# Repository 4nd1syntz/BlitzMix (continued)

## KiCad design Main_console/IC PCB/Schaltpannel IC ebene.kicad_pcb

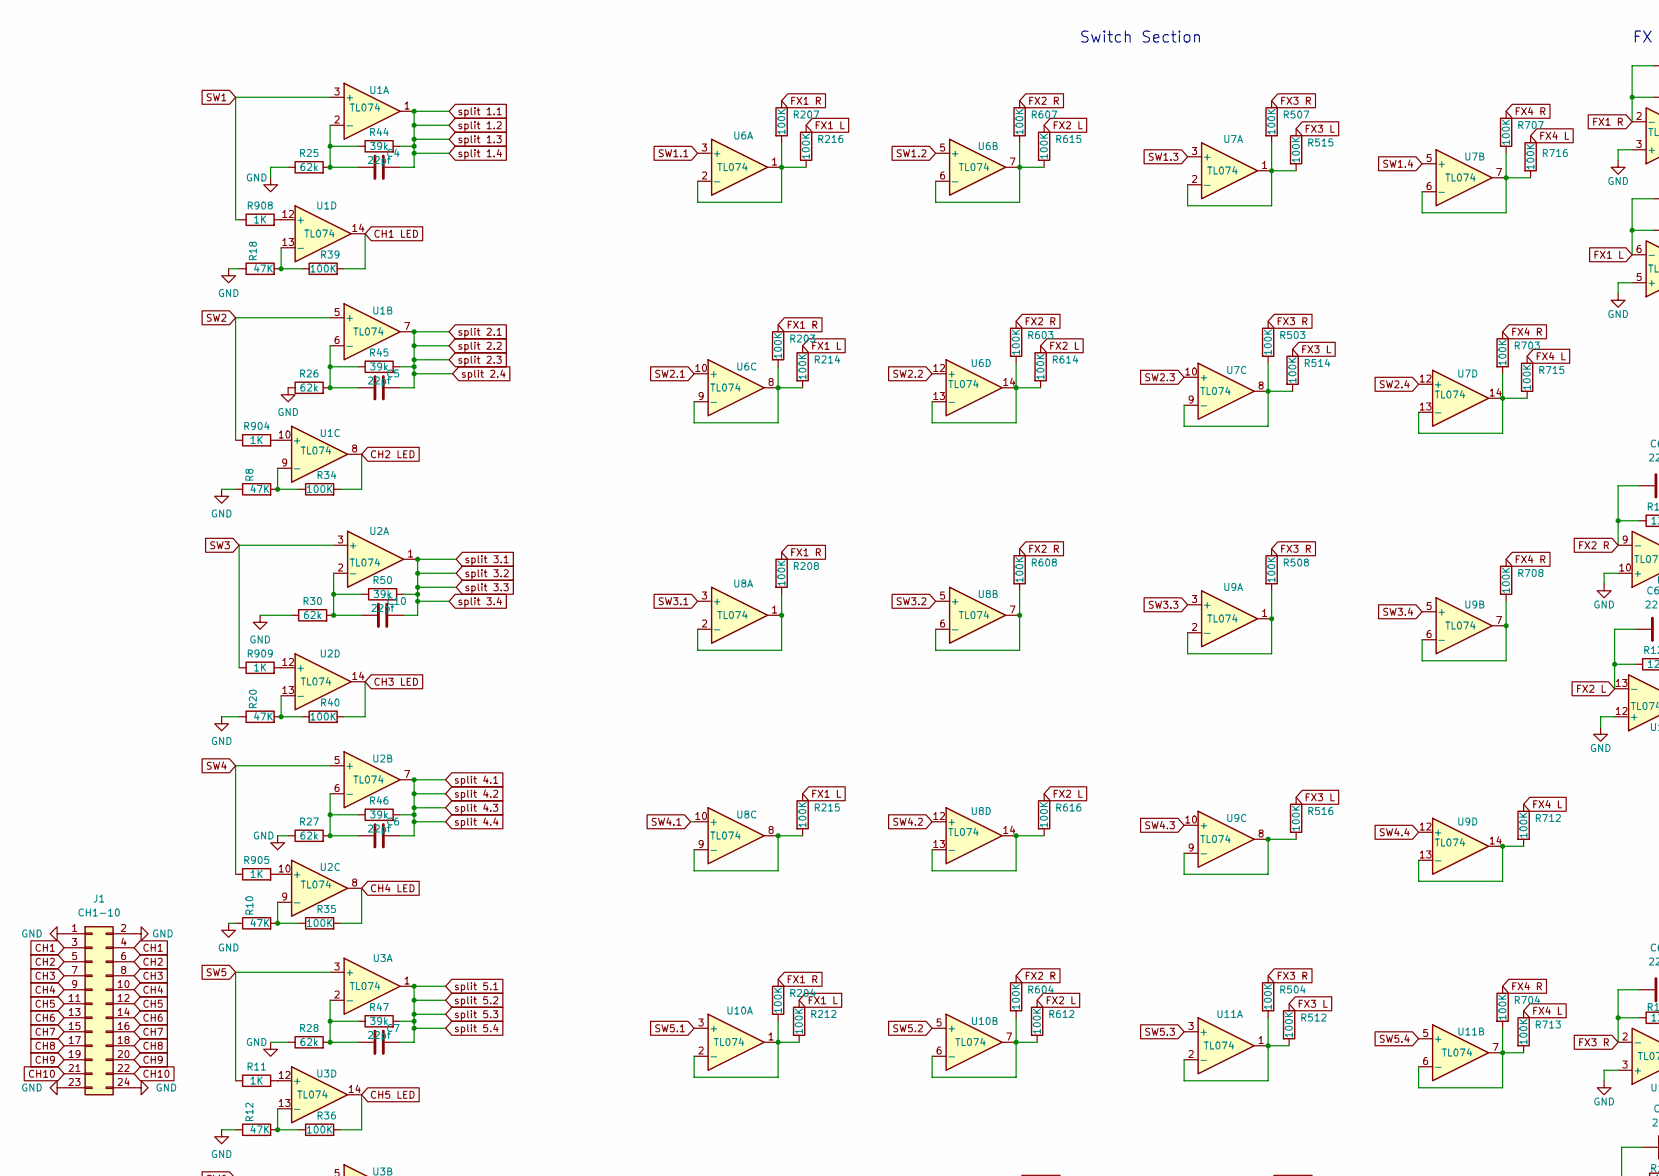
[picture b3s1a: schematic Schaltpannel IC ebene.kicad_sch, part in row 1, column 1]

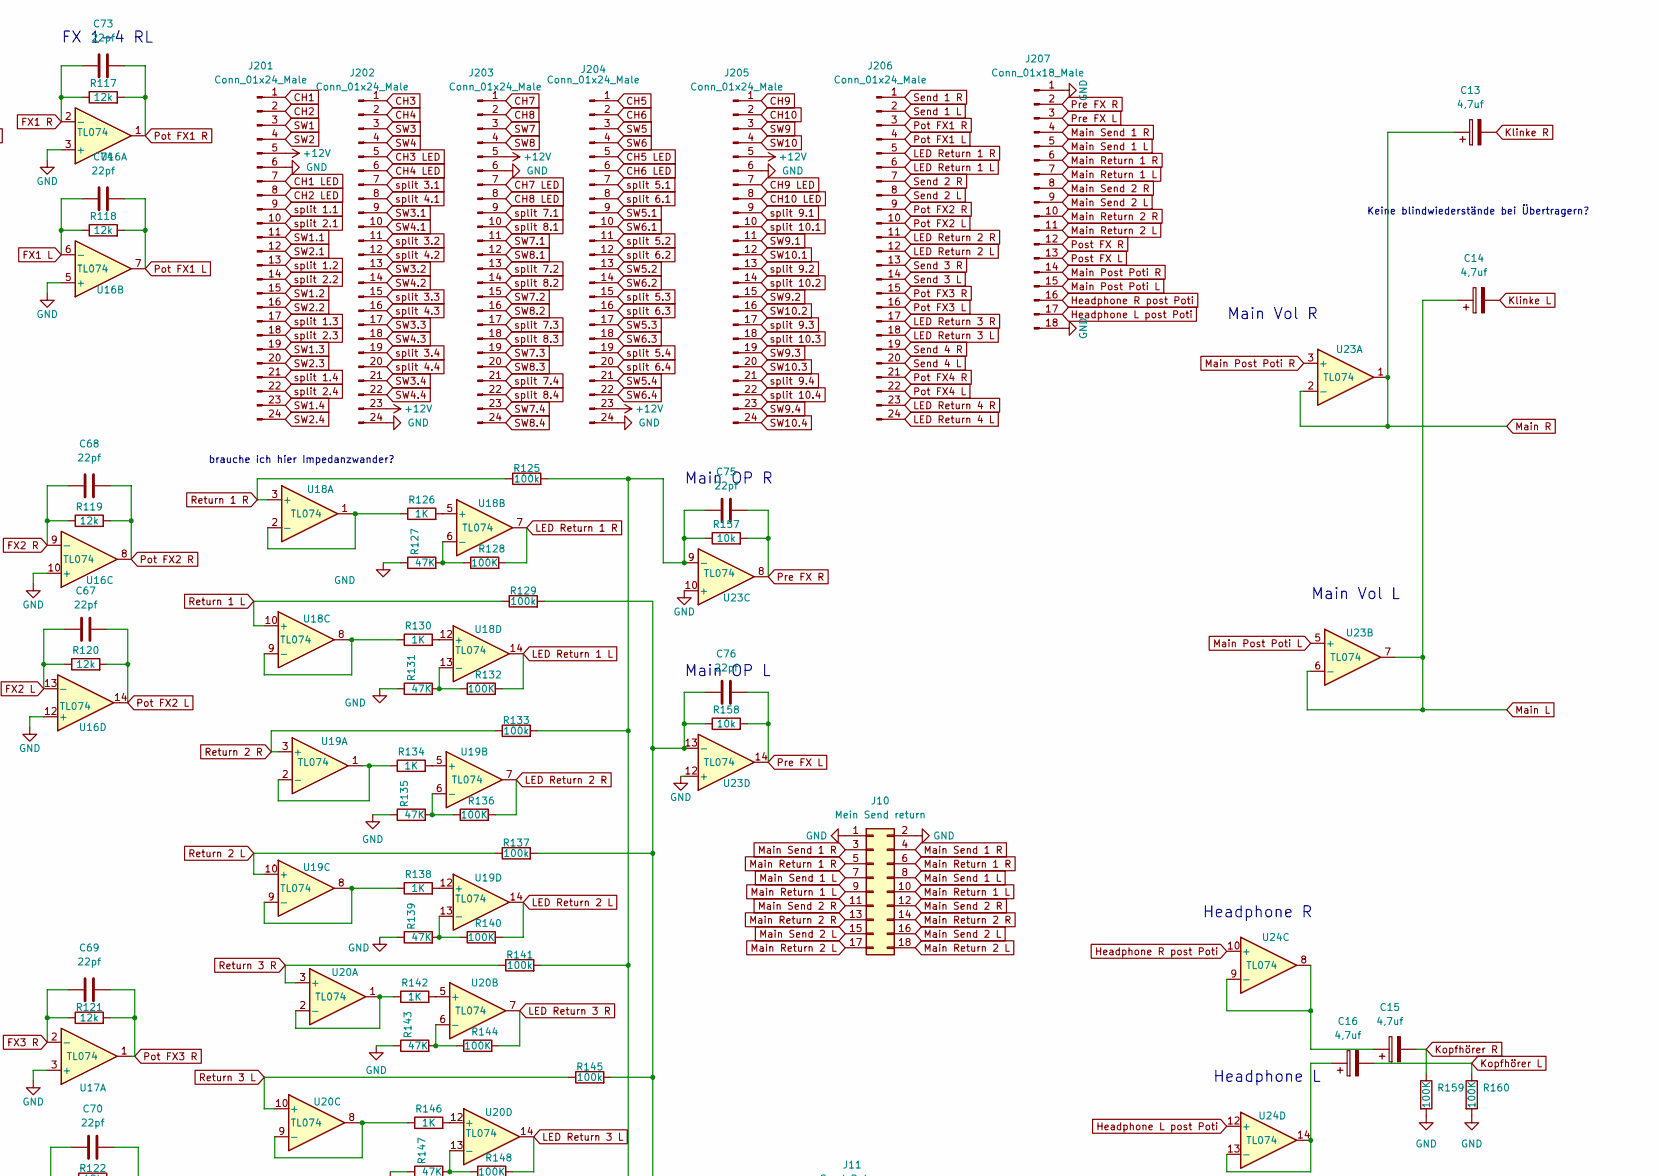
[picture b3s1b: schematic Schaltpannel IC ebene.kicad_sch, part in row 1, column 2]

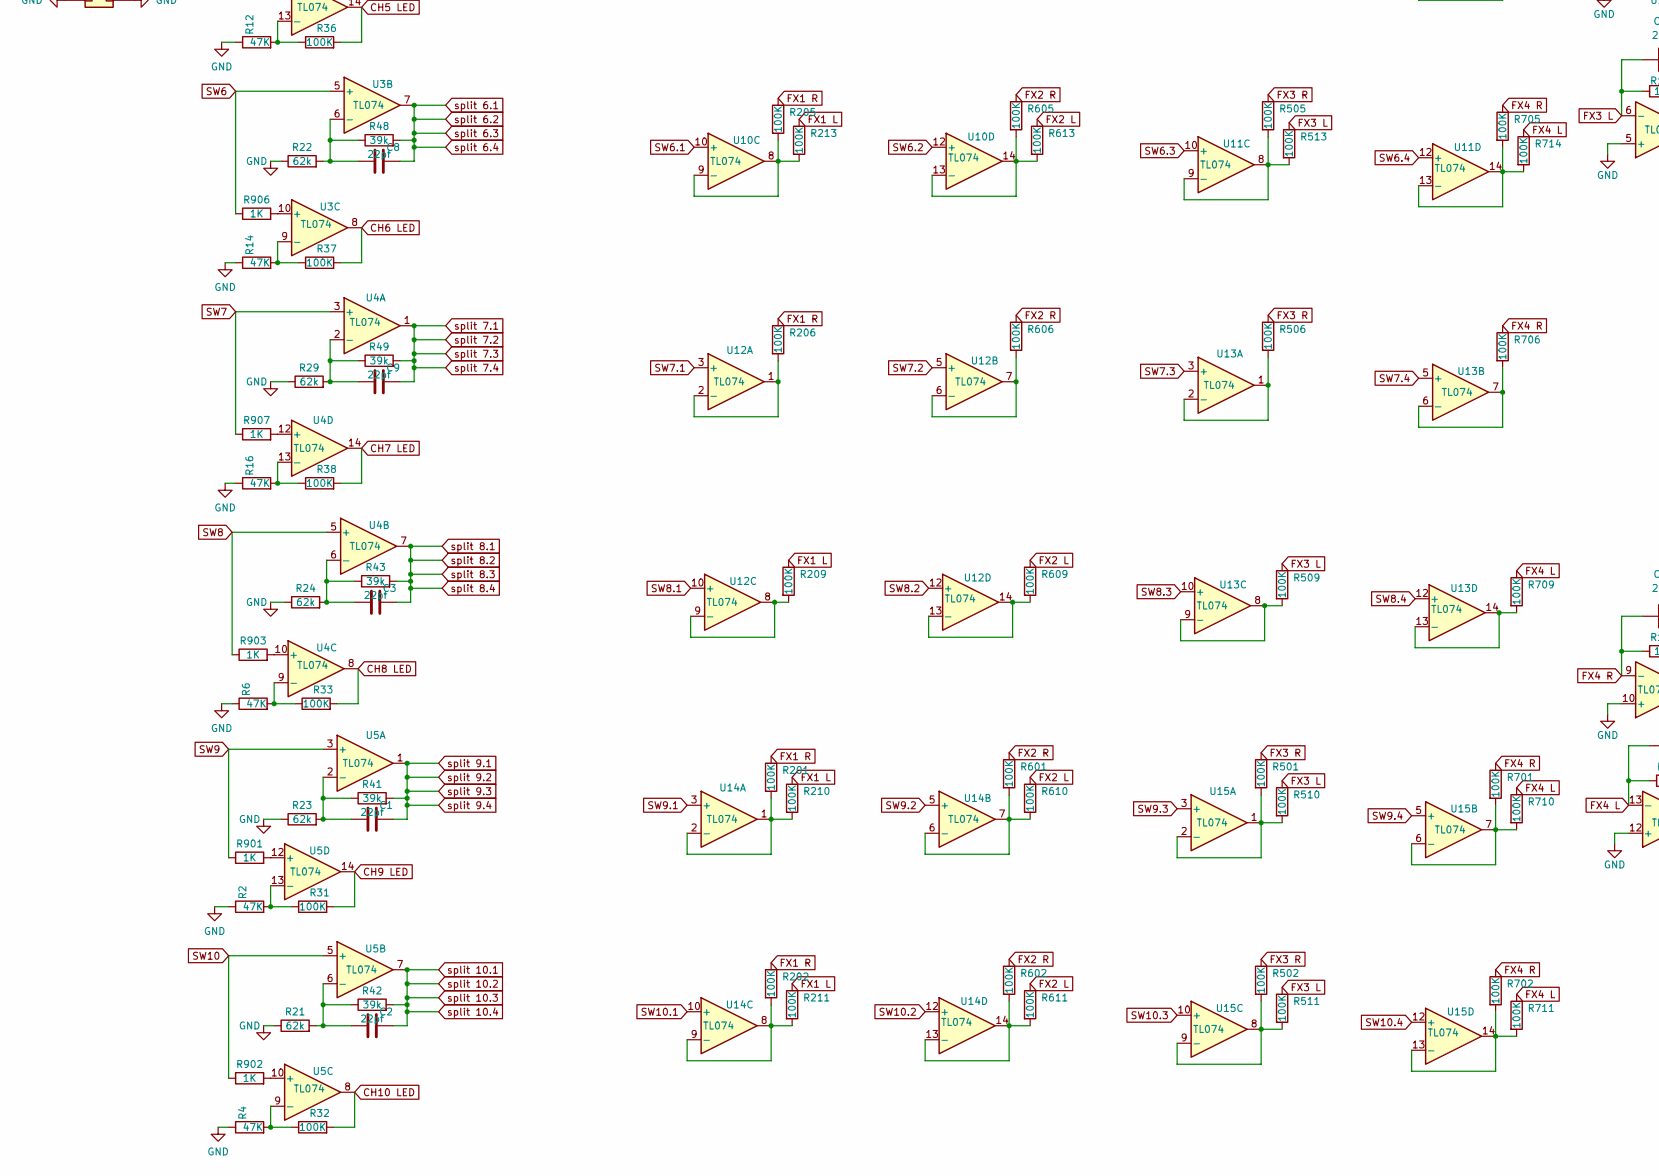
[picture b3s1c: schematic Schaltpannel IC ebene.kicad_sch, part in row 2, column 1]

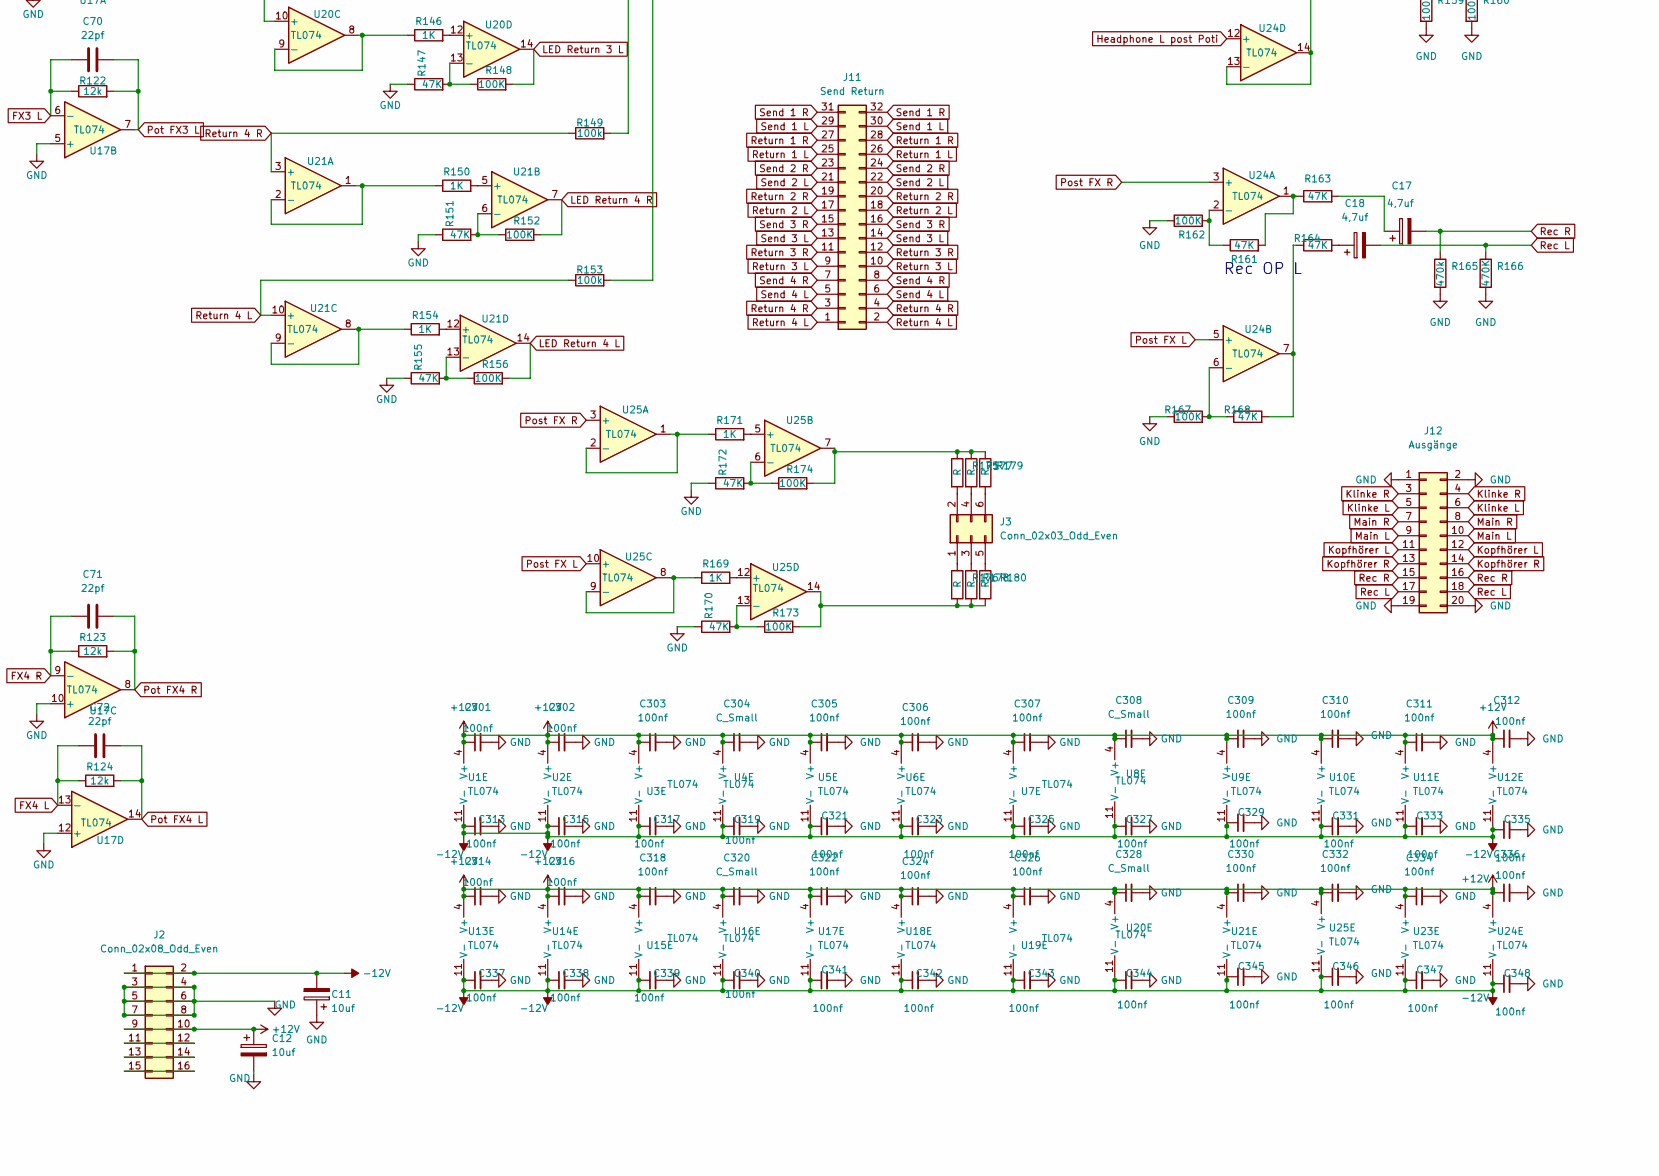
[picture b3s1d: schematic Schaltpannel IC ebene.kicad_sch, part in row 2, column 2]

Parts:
C1, C2, C3, C4, C5, C6, C7, C8, C9, C10, C67, C68, C69, C70, C71, C72, C73, C74, C75, C76: 22pf; C_0805_2012Metric
C11, C12: 10uf; CP_Elec_6.3x3.9
C13, C14, C15, C16, C17, C18: 4,7uf; CP_Elec_6.3x3.9
C301, C302, C303, C305, C306, C307, C309, C310, C311, C312, C313, C314, C315, C316, C317, C318, C319, C321, C322, C323, C324, C325, C326, C327, C329, C330, C331, C332, C333, C334, C335, C336, C337, C338, C339, C340, C341, C342, C343, C344, C345, C346, C347, C348: 100nf; C_Disc_D4.3mm_W1.9mm_P5.00mm
C304, C308, C320, C328: C_Small; C_Disc_D4.3mm_W1.9mm_P5.00mm
J1: CH1-10; PinSocket_2x12_P2.54mm_Vertical_SMD
J2: Conn_02x08_Odd_Even; PinSocket_2x08_P2.54mm_Vertical_SMD
J3: Conn_02x03_Odd_Even; PinSocket_2x03_P2.54mm_Vertical
J10: Mein Send return; PinSocket_2x10_P2.54mm_Vertical_SMD
J11: Send Return; PinSocket_2x17_P2.54mm_Vertical_SMD
J12: Ausgänge; PinSocket_2x10_P2.54mm_Vertical_SMD
J201, J202, J203, J204, J205, J206: Conn_01x24_Male; PinHeader_1x24_P2.54mm_Vertical
J207: Conn_01x18_Male; PinHeader_1x18_P2.54mm_Vertical
R2, R4, R6, R8, R10, R12, R14, R16, R18, R20, R127, R131, R135, R139, R143, R147, R151, R155, R161, R163, R164, R168, R170, R172: 47K; R_0805_2012Metric
R11, R126, R130, R134, R138, R142, R146, R150, R154, R169, R171: 1K; R_0805_2012Metric
R21, R22, R23, R24, R25, R26, R27, R28, R29, R30: 62k; R_0805_2012Metric
R31, R32, R33, R34, R35, R36, R37, R38, R39, R40, R128, R132, R136, R140, R144, R148, R152, R156, R159, R160, R162, R167, R173, R174: 100K; R_0805_2012Metric
R41, R42, R43, R44, R45, R46, R47, R48, R49, R50: 39k; R_0805_2012Metric
R117, R118, R119, R120, R121, R122, R123, R124: 12k; R_0805_2012Metric
R125, R129, R133, R137, R141, R145, R149, R153: 100k; R_0805_2012Metric
R157, R158: 10k; R_0805_2012Metric
R165: 470k; R_0805_2012Metric
R166: 470K; R_0805_2012Metric
R175, R176, R177, R178, R179, R180: R; R_0805_2012Metric
R201, R202, R203, R204, R205, R206, R207, R208, R209, R210, R211, R212, R213, R214, R215, R216, R501, R502, R503, R504, R505, R506, R507, R508, R509, R510, R511, R512, R513, R514, R515, R516: 100K; R_Axial_DIN0309_L9.0mm_D3.2mm_P12.70mm_Horizontal
R601, R602, R603, R604, R605, R606, R607, R608, R609, R610, R611, R612, R613, R614, R615, R616, R701, R702, R703, R704, R705, R706, R707, R708, R709, R710, R711, R712, R713, R714, R715, R716: 100K; R_Axial_DIN0207_L6.3mm_D2.5mm_P7.62mm_Horizontal
R901, R902, R903, R904, R905, R906, R907, R908, R909: 1K; R_Axial_DIN0207_L6.3mm_D2.5mm_P15.24mm_Horizontal
U1, U2, U3, U4, U5, U6, U7, U8, U9, U10, U11, U12, U13, U14, U15, U16, U17, U18, U19, U20, U21, U23, U24, U25: TL074; SOIC-14_3.9x8.7mm_P1.27mm

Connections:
+12V: C12.1, C301.1, C302.1, C303.1, C304.1, C305.1, C306.1, C307.1, C308.1, C309.1, C310.1, C311.1, C312.1, C314.1, C316.1, C318.1, C320.1, C322.1, C324.1, C326.1, C328.1, C330.1, C332.1, C334.1, C336.1, J2.9, J2.10, J201.5, J202.23, J203.5, J204.23, J205.5, U1.4 (V+), U2.4 (V+), U3.4 (V+), U4.4 (V+), U5.4 (V+), U6.4 (V+), U7.4 (V+), U8.4 (V+), U9.4 (V+), U10.4 (V+), U11.4 (V+), U12.4 (V+), U13.4 (V+), U14.4 (V+), U15.4 (V+), U16.4 (V+), U17.4 (V+), U18.4 (V+), U19.4 (V+), U20.4 (V+), U21.4 (V+), U23.4 (V+), U24.4 (V+), U25.4 (V+)
-12V: C11.2, C313.1, C315.1, C317.1, C319.1, C321.1, C323.1, C325.1, C327.1, C329.1, C331.1, C333.1, C335.1, C337.1, C338.1, C339.1, C340.1, C341.1, C342.1, C343.1, C344.1, C345.1, C346.1, C347.1, C348.1, J2.1, J2.2, U1.11 (V-), U2.11 (V-), U3.11 (V-), U4.11 (V-), U5.11 (V-), U6.11 (V-), U7.11 (V-), U8.11 (V-), U9.11 (V-), U10.11 (V-), U11.11 (V-), U12.11 (V-), U13.11 (V-), U14.11 (V-), U15.11 (V-), U16.11 (V-), U17.11 (V-), U18.11 (V-), U19.11 (V-), U20.11 (V-), U21.11 (V-), U23.11 (V-), U24.11 (V-), U25.11 (V-)
CH1: J1.3, J1.4, J201.1
CH1 LED: J201.7, R39.2, U1.14
CH2: J1.5, J1.6, J201.2
CH2 LED: J201.8, R34.2, U1.8
CH3: J1.7, J1.8, J202.1
CH3 LED: J202.5, R40.2, U2.14
CH4: J1.9, J1.10, J202.2
CH4 LED: J202.6, R35.2, U2.8
CH5: J1.11, J1.12, J204.1
CH5 LED: J204.5, R36.2, U3.14
CH6: J1.13, J1.14, J204.2
CH6 LED: J204.6, R37.2, U3.8
CH7: J1.15, J1.16, J203.1
CH7 LED: J203.7, R38.2, U4.14
CH8: J1.17, J1.18, J203.2
CH8 LED: J203.8, R33.2, U4.8
CH9: J1.19, J1.20, J205.1
CH9 LED: J205.7, R31.2, U5.14
CH10: J1.21, J1.22, J205.2
CH10 LED: J205.8, R32.2, U5.8
FX1 L: C74.1, R118.1, R209.1, R210.1, R211.1, R212.1, R213.1, R214.1, R215.1, R216.1, U16.6 (-)
FX1 R: C73.1, R117.1, R201.1, R202.1, R203.1, R204.1, R205.1, R206.1, R207.1, R208.1, U16.2 (-)
FX2 L: C67.1, R120.1, R609.1, R610.1, R611.1, R612.1, R613.1, R614.1, R615.1, R616.1, U16.13 (-)
FX2 R: C68.1, R119.1, R601.1, R602.1, R603.1, R604.1, R605.1, R606.1, R607.1, R608.1, U16.9 (-)
FX3 L: C70.1, R122.1, R509.1, R510.1, R511.1, R512.1, R513.1, R514.1, R515.1, R516.1, U17.6 (-)
FX3 R: C69.1, R121.1, R501.1, R502.1, R503.1, R504.1, R505.1, R506.1, R507.1, R508.1, U17.2 (-)
FX4 L: C72.1, R124.1, R709.1, R710.1, R711.1, R712.1, R713.1, R714.1, R715.1, R716.1, U17.13 (-)
FX4 R: C71.1, R123.1, R701.1, R702.1, R703.1, R704.1, R705.1, R706.1, R707.1, R708.1, U17.9 (-)
GND: C11.1, C12.2, C301.2, C302.2, C303.2, C304.2, C305.2, C306.2, C307.2, C308.2, C309.2, C310.2, C311.2, C312.2, C313.2, C314.2, C315.2, C316.2, C317.2, C318.2, C319.2, C320.2, C321.2, C322.2, C323.2, C324.2, C325.2, C326.2, C327.2, C328.2, C329.2, C330.2, C331.2, C332.2, C333.2, C334.2, C335.2, C336.2, C337.2, C338.2, C339.2, C340.2, C341.2, C342.2, C343.2, C344.2, C345.2, C346.2, C347.2, C348.2, J1.1, J1.2, J1.23, J1.24, J2.3, J2.4, J2.5, J2.6, J2.7, J2.8, J10.1, J10.2, J12.1, J12.2, J12.19, J12.20, J201.6, J202.24, J203.6, J204.24, J205.6, J207.1, J207.18, R2.1, R4.1, R6.1, R8.1, R10.1, R12.1, R14.1, R16.1, R18.1, R20.1, R21.1, R22.1, R23.1, R24.1, R25.1, R26.1, R27.1, R28.1, R29.1, R30.1, R127.1, R131.1, R135.1, R139.1, R143.1, R147.1, R151.1, R155.1, R159.2, R160.2, R162.1, R165.2, R166.2, R167.1, R170.1, R172.1, U16.3 (+), U16.5 (+), U16.10 (+), U16.12 (+), U17.3 (+), U17.5 (+), U17.10 (+), U17.12 (+), U23.10 (+), U23.12 (+)
Headphone L post Poti: J207.17, U24.12 (+)
Headphone R post Poti: J207.16, U24.10 (+)
Klinke L: C14.2, J12.5, J12.6
Klinke R: C13.2, J12.3, J12.4
Kopfhörer L: C16.2, J12.11, J12.12, R160.1
Kopfhörer R: C15.2, J12.13, J12.14, R159.1
LED Return 1 L: J206.6, R132.2, U18.14
LED Return 1 R: J206.5, R128.2, U18.7
LED Return 2 L: J206.12, R140.2, U19.14
LED Return 2 R: J206.11, R136.2, U19.7
LED Return 3 L: J206.18, R148.2, U20.14
LED Return 3 R: J206.17, R144.2, U20.7
LED Return 4 L: J206.24, R156.2, U21.14
LED Return 4 R: J206.23, R152.2, U21.7
Main L: C14.1, J12.9, J12.10, U23.6 (-), U23.7
Main Post Poti L: J207.15, U23.5 (+)
Main Post Poti R: J207.14, U23.3 (+)
Main R: C13.1, J12.7, J12.8, U23.1, U23.2 (-)
Main Return 1 L: J10.9, J10.10, J207.7
Main Return 1 R: J10.5, J10.6, J207.6
Main Return 2 L: J10.17, J10.18, J207.11
Main Return 2 R: J10.13, J10.14, J207.10
Main Send 1 L: J10.7, J10.8, J207.5
Main Send 1 R: J10.3, J10.4, J207.4
Main Send 2 L: J10.15, J10.16, J207.9
Main Send 2 R: J10.11, J10.12, J207.8
unnamed: C1.1, R23.2, R41.1, U5.2 (-)
unnamed: C2.1, R21.2, R42.1, U5.6 (-)
unnamed: C3.1, R24.2, R43.1, U4.6 (-)
unnamed: C4.1, R25.2, R44.1, U1.2 (-)
unnamed: C5.1, R26.2, R45.1, U1.6 (-)
unnamed: C6.1, R27.2, R46.1, U2.6 (-)
unnamed: C7.1, R28.2, R47.1, U3.2 (-)
unnamed: C8.1, R22.2, R48.1, U3.6 (-)
unnamed: C9.1, R29.2, R49.1, U4.2 (-)
unnamed: C10.1, R30.2, R50.1, U2.2 (-)
unnamed: C15.1, U24.8, U24.9 (-)
unnamed: C16.1, U24.13 (-), U24.14
unnamed: C17.1, R163.2
unnamed: C18.1, R164.2
unnamed: C75.1, R125.2, R133.2, R141.2, R149.2, R157.1, U23.9 (-)
unnamed: C76.1, R129.2, R137.2, R145.2, R153.2, R158.1, U23.13 (-)
unnamed: J2.11, J2.12
unnamed: J2.13, J2.14
unnamed: J2.15, J2.16
unnamed: J3.1, R176.1
unnamed: J3.2, R175.2
unnamed: J3.3, R178.1
unnamed: J3.4, R177.2
unnamed: J3.5, R180.1
unnamed: J3.6, R179.2
unnamed: R2.2, R31.1, U5.13 (-)
unnamed: R10.2, R35.1, U2.9 (-)
unnamed: R11.2, U3.12 (+)
unnamed: R12.2, R36.1, U3.13 (-)
unnamed: R14.2, R37.1, U3.9 (-)
unnamed: R16.2, R38.1, U4.13 (-)
unnamed: R18.2, R39.1, U1.13 (-)
unnamed: R20.2, R40.1, U2.13 (-)
unnamed: R4.2, R32.1, U5.9 (-)
unnamed: R6.2, R33.1, U4.9 (-)
unnamed: R8.2, R34.1, U1.9 (-)
unnamed: R126.1, U18.1, U18.2 (-)
unnamed: R126.2, U18.5 (+)
unnamed: R127.2, R128.1, U18.6 (-)
unnamed: R130.1, U18.8, U18.9 (-)
unnamed: R130.2, U18.12 (+)
unnamed: R131.2, R132.1, U18.13 (-)
unnamed: R134.1, U19.1, U19.2 (-)
unnamed: R134.2, U19.5 (+)
unnamed: R135.2, R136.1, U19.6 (-)
unnamed: R138.1, U19.8, U19.9 (-)
unnamed: R138.2, U19.12 (+)
unnamed: R139.2, R140.1, U19.13 (-)
unnamed: R142.1, U20.1, U20.2 (-)
unnamed: R142.2, U20.5 (+)
unnamed: R143.2, R144.1, U20.6 (-)
unnamed: R146.1, U20.8, U20.9 (-)
unnamed: R146.2, U20.12 (+)
unnamed: R147.2, R148.1, U20.13 (-)
unnamed: R150.1, U21.1, U21.2 (-)
unnamed: R150.2, U21.5 (+)
unnamed: R151.2, R152.1, U21.6 (-)
unnamed: R154.1, U21.8, U21.9 (-)
unnamed: R154.2, U21.12 (+)
unnamed: R155.2, R156.1, U21.13 (-)
unnamed: R161.1, R162.2, U24.2 (-)
unnamed: R161.2, R163.1, U24.1
unnamed: R164.1, R168.2, U24.7
unnamed: R167.2, R168.1, U24.6 (-)
unnamed: R169.1, U25.8, U25.9 (-)
unnamed: R169.2, U25.12 (+)
unnamed: R170.2, R173.1, U25.13 (-)
unnamed: R171.1, U25.1, U25.2 (-)
unnamed: R171.2, U25.5 (+)
unnamed: R172.2, R174.1, U25.6 (-)
unnamed: R173.2, R176.2, R178.2, R180.2, U25.14
unnamed: R174.2, R175.1, R177.1, R179.1, U25.7
unnamed: R201.2, R210.2, U14.1, U14.2 (-)
unnamed: R202.2, R211.2, U14.8, U14.9 (-)
unnamed: R203.2, R214.2, U6.8, U6.9 (-)
unnamed: R204.2, R212.2, U10.1, U10.2 (-)
unnamed: R205.2, R213.2, U10.8, U10.9 (-)
unnamed: R206.2, U12.1, U12.2 (-)
unnamed: R207.2, R216.2, U6.1, U6.2 (-)
unnamed: R208.2, U8.1, U8.2 (-)
unnamed: R209.2, U12.8, U12.9 (-)
unnamed: R215.2, U8.8, U8.9 (-)
unnamed: R501.2, R510.2, U15.1, U15.2 (-)
unnamed: R502.2, R511.2, U15.8, U15.9 (-)
unnamed: R503.2, R514.2, U7.8, U7.9 (-)
unnamed: R504.2, R512.2, U11.1, U11.2 (-)
unnamed: R505.2, R513.2, U11.8, U11.9 (-)
unnamed: R506.2, U13.1, U13.2 (-)
unnamed: R507.2, R515.2, U7.1, U7.2 (-)
unnamed: R508.2, U9.1, U9.2 (-)
unnamed: R509.2, U13.8, U13.9 (-)
unnamed: R516.2, U9.8, U9.9 (-)
unnamed: R601.2, R610.2, U14.6 (-), U14.7
unnamed: R602.2, R611.2, U14.13 (-), U14.14
unnamed: R603.2, R614.2, U6.13 (-), U6.14
unnamed: R604.2, R612.2, U10.6 (-), U10.7
unnamed: R605.2, R613.2, U10.13 (-), U10.14
unnamed: R606.2, U12.6 (-), U12.7
unnamed: R607.2, R615.2, U6.6 (-), U6.7
unnamed: R608.2, U8.6 (-), U8.7
unnamed: R609.2, U12.13 (-), U12.14
unnamed: R616.2, U8.13 (-), U8.14
unnamed: R701.2, R710.2, U15.6 (-), U15.7
unnamed: R702.2, R711.2, U15.13 (-), U15.14
unnamed: R703.2, R715.2, U7.13 (-), U7.14
unnamed: R704.2, R713.2, U11.6 (-), U11.7
unnamed: R705.2, R714.2, U11.13 (-), U11.14
unnamed: R706.2, U13.6 (-), U13.7
unnamed: R707.2, R716.2, U7.6 (-), U7.7
unnamed: R708.2, U9.6 (-), U9.7
unnamed: R709.2, U13.13 (-), U13.14
unnamed: R712.2, U9.13 (-), U9.14
unnamed: R901.2, U5.12 (+)
unnamed: R902.2, U5.10 (+)
unnamed: R903.2, U4.10 (+)
unnamed: R904.2, U1.10 (+)
unnamed: R905.2, U2.10 (+)
unnamed: R906.2, U3.10 (+)
unnamed: R907.2, U4.12 (+)
unnamed: R908.2, U1.12 (+)
unnamed: R909.2, U2.12 (+)
Post FX L: J207.13, U24.5 (+), U25.10 (+)
Post FX R: J207.12, U24.3 (+), U25.3 (+)
Pot FX1 L: C74.2, J206.4, R118.2, U16.7
Pot FX1 R: C73.2, J206.3, R117.2, U16.1
Pot FX2 L: C67.2, J206.10, R120.2, U16.14
Pot FX2 R: C68.2, J206.9, R119.2, U16.8
Pot FX3 L: C70.2, J206.16, R122.2, U17.7
Pot FX3 R: C69.2, J206.15, R121.2, U17.1
Pot FX4 L: C72.2, J206.22, R124.2, U17.14
Pot FX4 R: C71.2, J206.21, R123.2, U17.8
Pre FX L: C76.2, J207.3, R158.2, U23.14
Pre FX R: C75.2, J207.2, R157.2, U23.8
Rec L: C18.2, J12.17, J12.18, R166.1
Rec R: C17.2, J12.15, J12.16, R165.1
Return 1 L: J11.25, J11.26, R129.1, U18.10 (+)
Return 1 R: J11.27, J11.28
Return 1 R: R125.1, U18.3 (+)
Return 2 L: J11.17, J11.18, R137.1, U19.10 (+)
Return 2 R: J11.19, J11.20
Return 2 R: R133.1, U19.3 (+)
Return 3 L: J11.9, J11.10, R145.1, U20.10 (+)
Return 3 R: J11.11, J11.12, R141.1, U20.3 (+)
Return 4 L: J11.1, J11.2, R153.1, U21.10 (+)
Return 4 R: J11.3, J11.4, R149.1, U21.3 (+)
SW1: J201.3, R908.1, U1.3 (+)
SW1.1: J201.11, U6.3 (+)
SW1.2: J201.15, U6.5 (+)
SW1.3: J201.19, U7.3 (+)
SW1.4: J201.23, U7.5 (+)
SW2: J201.4, R904.1, U1.5 (+)
SW2.1: J201.12, U6.10 (+)
SW2.2: J201.16, U6.12 (+)
SW2.3: J201.20, U7.10 (+)
SW2.4: J201.24, U7.12 (+)
SW3: J202.3, R909.1, U2.3 (+)
SW3.1: J202.9, U8.3 (+)
SW3.2: J202.13, U8.5 (+)
SW3.3: J202.17, U9.3 (+)
SW3.4: J202.21, U9.5 (+)
SW4: J202.4, R905.1, U2.5 (+)
SW4.1: J202.10, U8.10 (+)
SW4.2: J202.14, U8.12 (+)
SW4.3: J202.18, U9.10 (+)
SW4.4: J202.22, U9.12 (+)
SW5: J204.3, R11.1, U3.3 (+)
SW5.1: J204.9, U10.3 (+)
SW5.2: J204.13, U10.5 (+)
SW5.3: J204.17, U11.3 (+)
SW5.4: J204.21, U11.5 (+)
SW6: J204.4, R906.1, U3.5 (+)
SW6.1: J204.10, U10.10 (+)
SW6.2: J204.14, U10.12 (+)
SW6.3: J204.18, U11.10 (+)
SW6.4: J204.22, U11.12 (+)
SW7: J203.3, R907.1, U4.3 (+)
SW7.1: J203.11, U12.3 (+)
SW7.2: J203.15, U12.5 (+)
SW7.3: J203.19, U13.3 (+)
SW7.4: J203.23, U13.5 (+)
SW8: J203.4, R903.1, U4.5 (+)
SW8.1: J203.12, U12.10 (+)
SW8.2: J203.16, U12.12 (+)
SW8.3: J203.20, U13.10 (+)
SW8.4: J203.24, U13.12 (+)
SW9: J205.3, R901.1, U5.3 (+)
SW9.1: J205.11, U14.3 (+)
SW9.2: J205.15, U14.5 (+)
SW9.3: J205.19, U15.3 (+)
SW9.4: J205.23, U15.5 (+)
SW10: J205.4, R902.1, U5.5 (+)
SW10.1: J205.12, U14.10 (+)
SW10.2: J205.16, U14.12 (+)
SW10.3: J205.20, U15.10 (+)
SW10.4: J205.24, U15.12 (+)
Send 1 L: J11.29, J11.30, J206.2
Send 1 R: J11.31, J11.32, J206.1
Send 2 L: J11.21, J11.22, J206.8
Send 2 R: J11.23, J11.24, J206.7
Send 3 L: J11.13, J11.14, J206.14
Send 3 R: J11.15, J11.16, J206.13
Send 4 L: J11.5, J11.6, J206.20
Send 4 R: J11.7, J11.8, J206.19
split 1.1: C4.2, J201.9, J201.13, J201.17, J201.21, R44.2, U1.1
split 2.1: C5.2, J201.10, J201.14, J201.18, J201.22, R45.2, U1.7
split 3.1: C10.2, J202.7, J202.11, J202.15, J202.19, R50.2, U2.1
split 4.1: C6.2, J202.8, J202.12, J202.16, J202.20, R46.2, U2.7
split 5.1: C7.2, J204.7, J204.11, J204.15, J204.19, R47.2, U3.1
split 6.1: C8.2, J204.8, J204.12, J204.16, J204.20, R48.2, U3.7
split 7.1: C9.2, J203.9, J203.13, J203.17, J203.21, R49.2, U4.1
split 8.1: C3.2, J203.10, J203.14, J203.18, J203.22, R43.2, U4.7
split 9.1: C1.2, J205.9, J205.13, J205.17, J205.21, R41.2, U5.1
split 10.1: C2.2, J205.10, J205.14, J205.18, J205.22, R42.2, U5.7

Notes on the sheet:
Main Vol R
Keine blindwiederstände bei Übertragern?
Main OP R
Headphone R
Rec OP L
Switch Section
Headphone L
Main Vol L
FX 1-4 RL
brauche ich hier Impedanzwander?
Main OP L

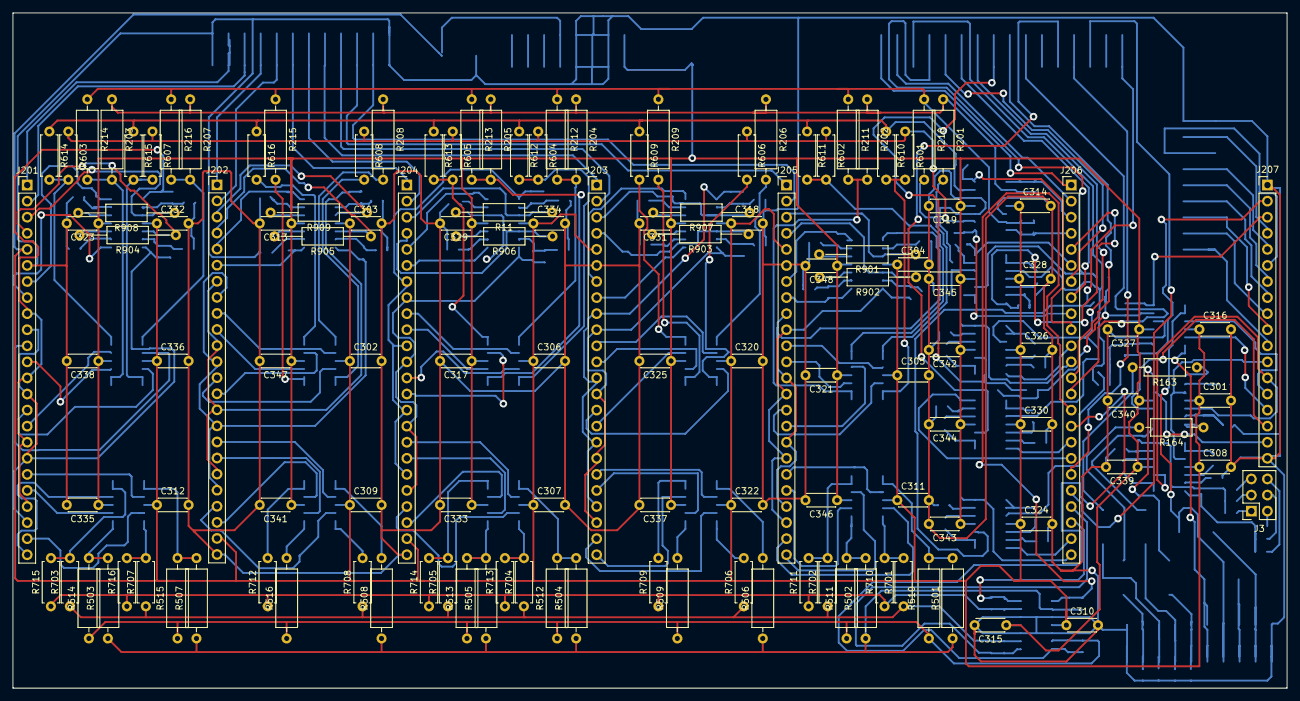
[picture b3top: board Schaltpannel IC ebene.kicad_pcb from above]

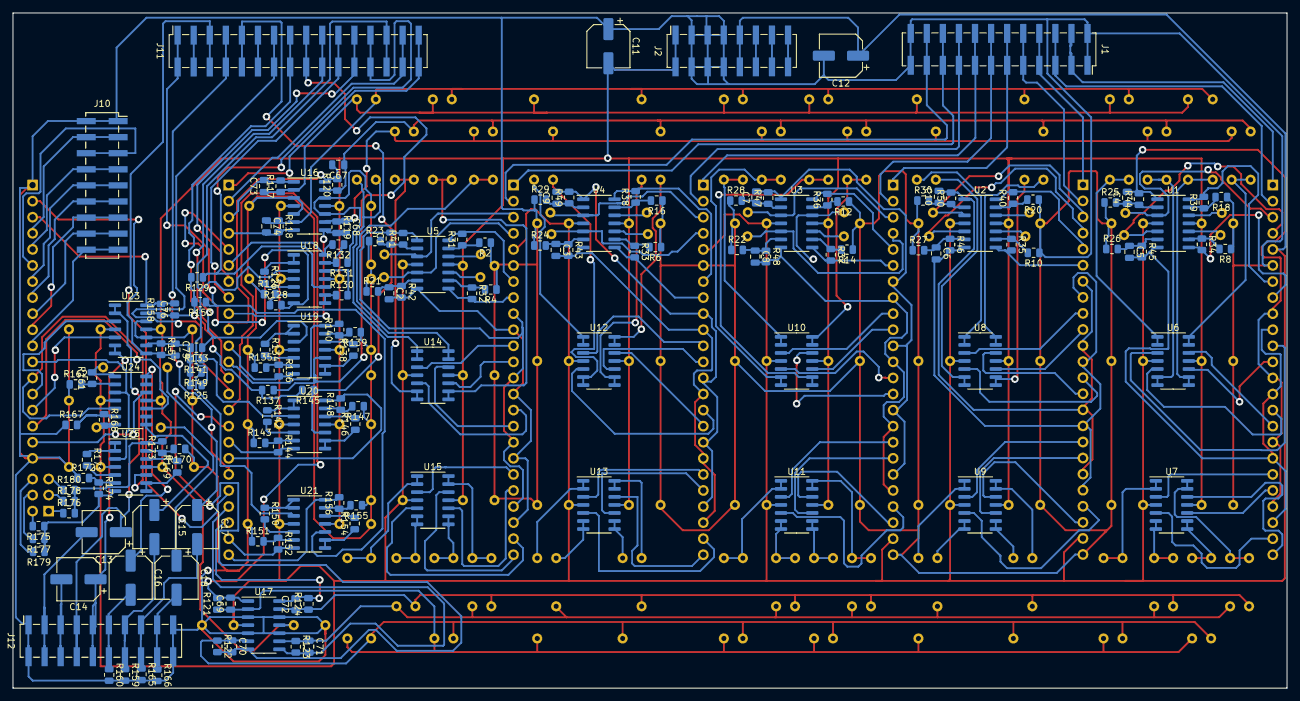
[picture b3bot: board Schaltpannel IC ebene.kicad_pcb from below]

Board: 2 copper layers, 201.3 x 106.7 mm, 291 parts (159 on the bottom side), 270 nets.

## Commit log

2022-12-19 Deleted backups
2022-12-20 Add files via upload
    Frontpannels
